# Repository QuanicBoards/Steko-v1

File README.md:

# Steko-v1
The original Steko Stenography keyboard. This repo contains KiCad PCB files for the design.

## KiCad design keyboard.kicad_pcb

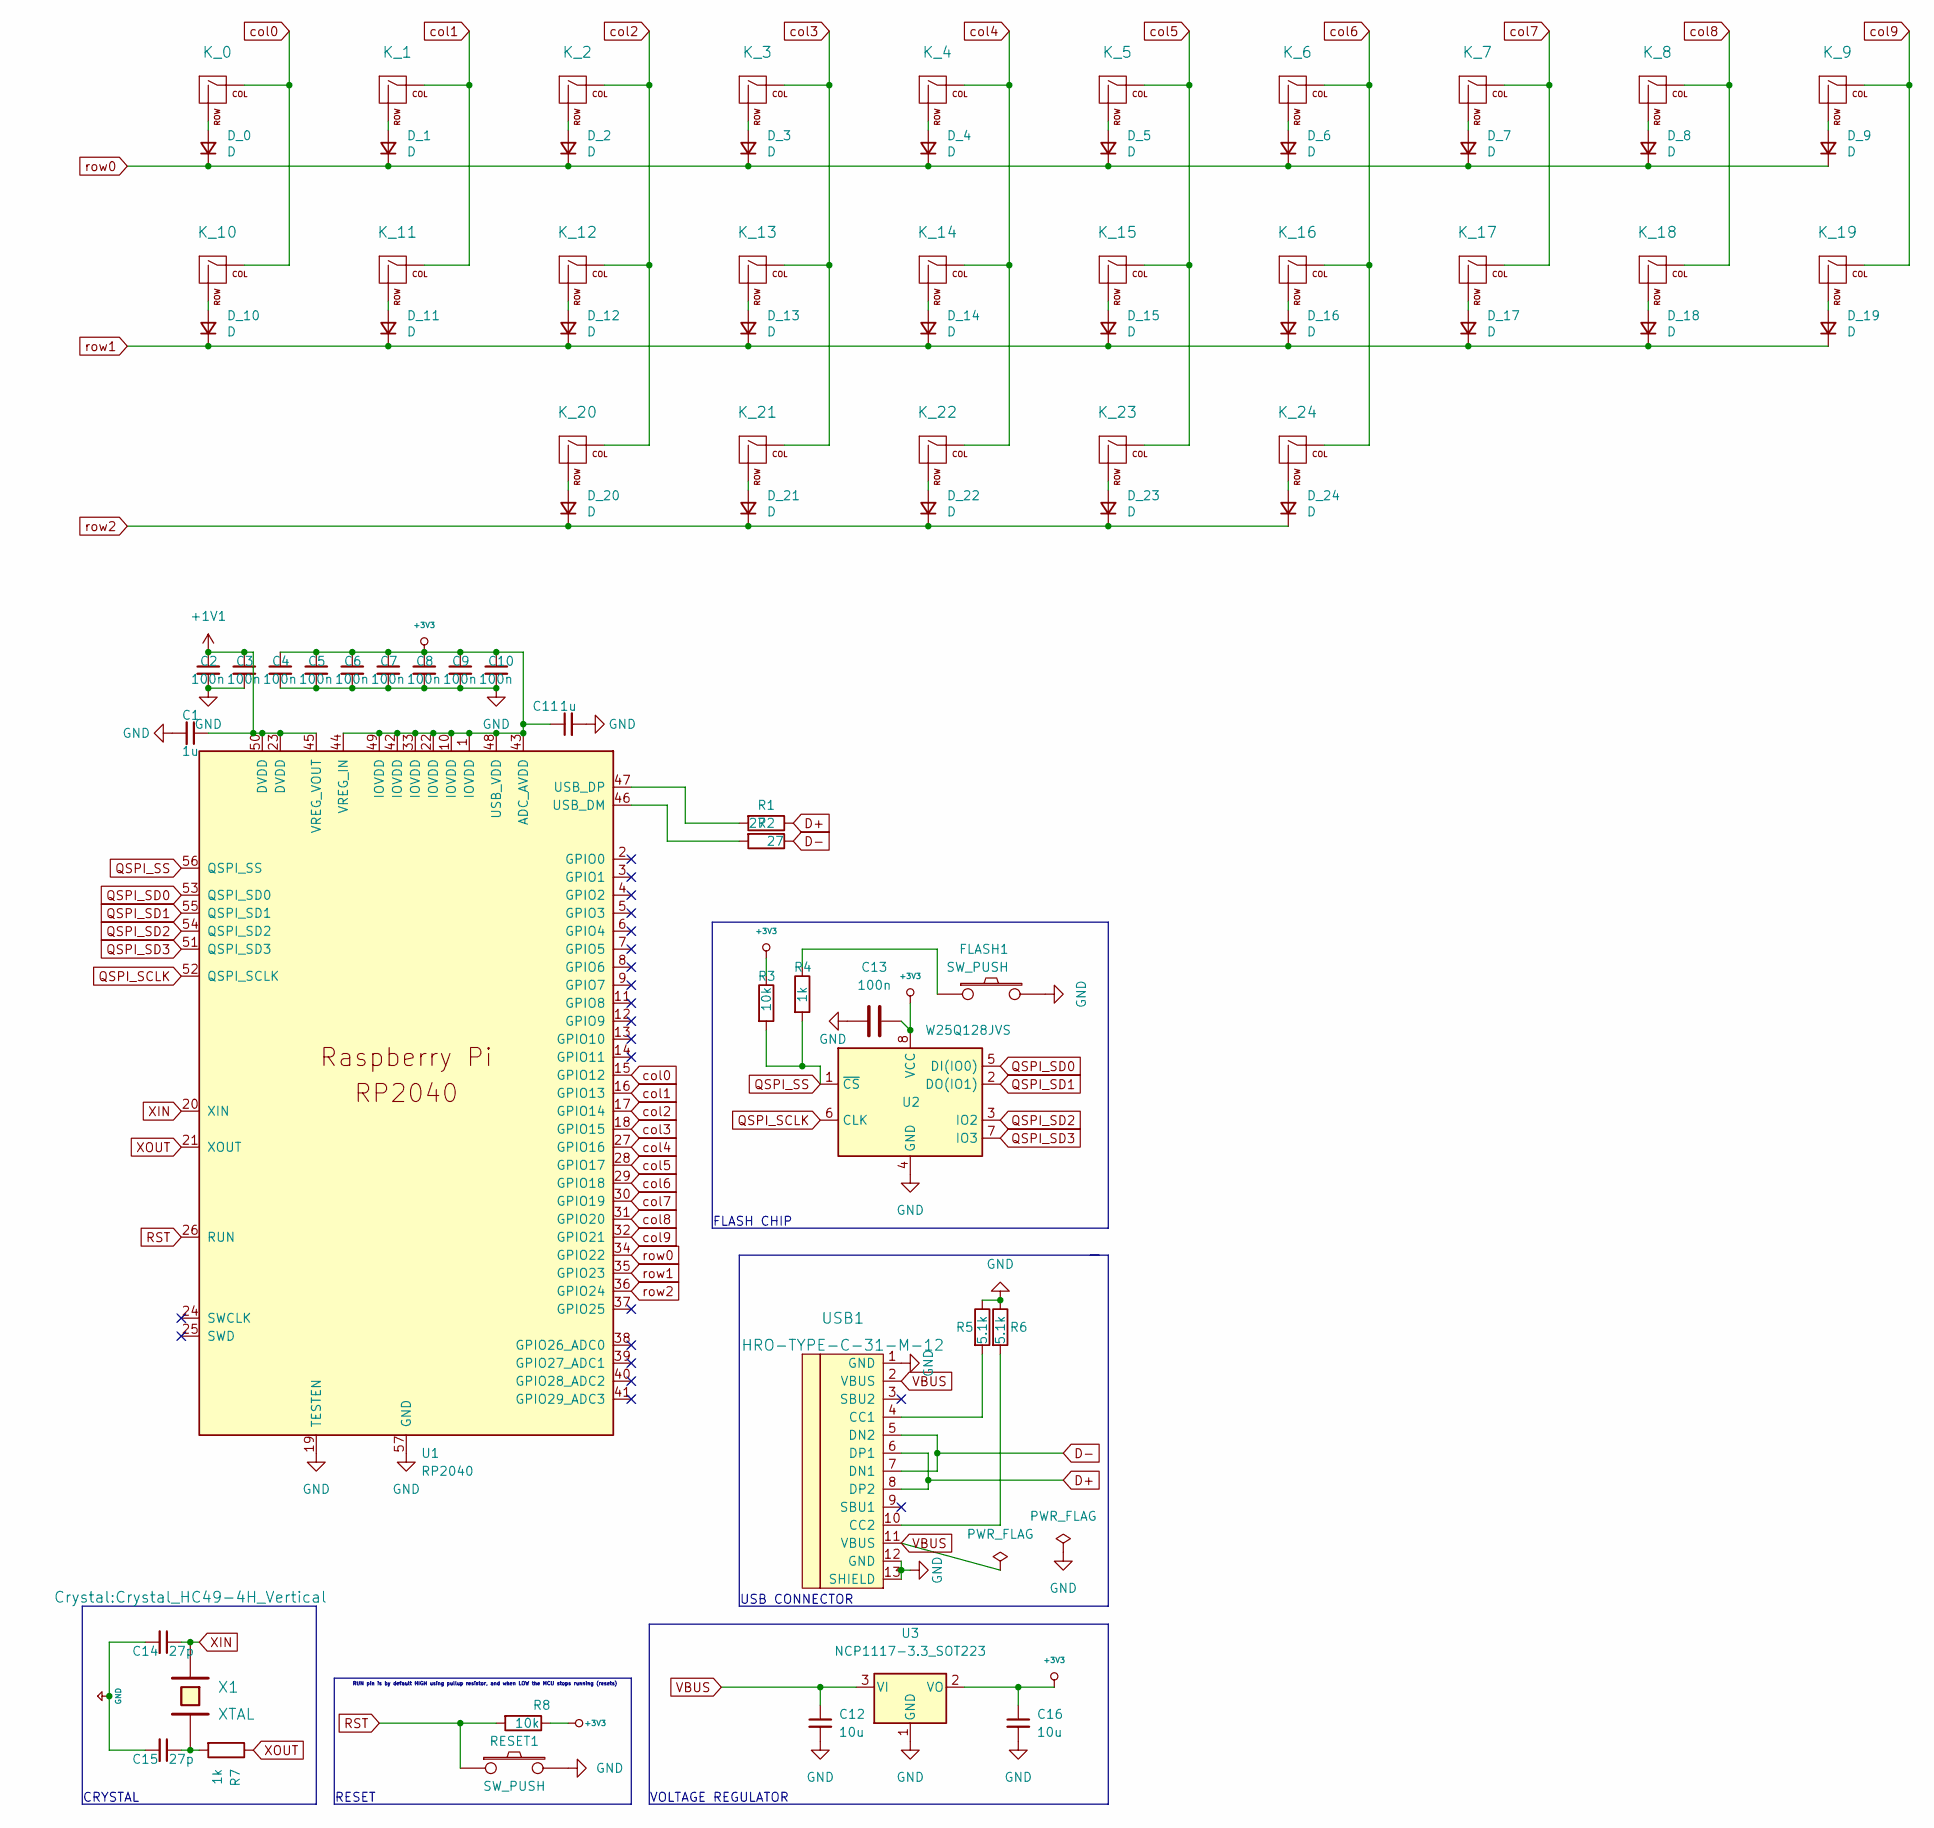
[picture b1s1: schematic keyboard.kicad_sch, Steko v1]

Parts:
C1, C11: 1u; C_1206_3216Metric
C2, C3, C4, C5, C6, C7, C8, C9, C10: 100n; C_1206_3216Metric
C12, C16: 10u; C_1206_3216Metric
C13: 100n; C_1206_3216Metric; LCSC C60474
C14, C15: 27p; C_1206_3216Metric
D_0, D_1, D_2, D_3, D_4, D_5, D_6, D_7, D_8, D_9, D_10, D_11, D_12, D_13, D_14, D_15, D_16, D_17, D_18, D_19, D_20, D_21, D_22, D_23, D_24: D; D_SOD-123
FLASH1: SW_PUSH; SW_SPST_PTS645
K_0, K_1, K_2, K_3, K_4, K_5, K_6, K_7, K_8, K_9, K_10, K_11, K_12, K_13, K_14, K_15, K_16, K_17, K_18, K_19, K_20, K_21, K_22, K_23, K_24: KEYSW; MX-1U-NoLED
R1, R2: 27; R_1206_3216Metric
R3, R8: 10k; R_1206_3216Metric
R4, R7: 1k; R_1206_3216Metric
R5, R6: 5.1k; R_1206_3216Metric
RESET1: SW_PUSH; SW_SPST_PTS645
U1: RP2040; RP2040-QFN-56
U2: W25Q128JVS; SOIC-8_5.23x5.23mm_P1.27mm; LCSC C113767
U3: NCP1117-3.3_SOT223; SOT-223-3_TabPin2
USB1: HRO-TYPE-C-31-M-12
X1: XTAL; Crystal_HC49-4H_Vertical

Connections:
+1V1: C1.1, C2.1, C3.1, U1.23 (DVDD), U1.45 (VREG_VOUT), U1.50 (DVDD)
D+: R1.1, USB1.6 (DP1), USB1.8 (DP2)
D-: R2.1, USB1.5 (DN2), USB1.7 (DN1)
unnamed: C15.1, R7.2, X1.2
unnamed: D_0.2 (A), K_0.2 (ROW)
unnamed: D_1.2 (A), K_1.2 (ROW)
unnamed: D_2.2 (A), K_2.2 (ROW)
unnamed: D_3.2 (A), K_3.2 (ROW)
unnamed: D_4.2 (A), K_4.2 (ROW)
unnamed: D_5.2 (A), K_5.2 (ROW)
unnamed: D_6.2 (A), K_6.2 (ROW)
unnamed: D_7.2 (A), K_7.2 (ROW)
unnamed: D_8.2 (A), K_8.2 (ROW)
unnamed: D_9.2 (A), K_9.2 (ROW)
unnamed: D_10.2 (A), K_10.2 (ROW)
unnamed: D_11.2 (A), K_11.2 (ROW)
unnamed: D_12.2 (A), K_12.2 (ROW)
unnamed: D_13.2 (A), K_13.2 (ROW)
unnamed: D_14.2 (A), K_14.2 (ROW)
unnamed: D_15.2 (A), K_15.2 (ROW)
unnamed: D_16.2 (A), K_16.2 (ROW)
unnamed: D_17.2 (A), K_17.2 (ROW)
unnamed: D_18.2 (A), K_18.2 (ROW)
unnamed: D_19.2 (A), K_19.2 (ROW)
unnamed: D_20.2 (A), K_20.2 (ROW)
unnamed: D_21.2 (A), K_21.2 (ROW)
unnamed: D_22.2 (A), K_22.2 (ROW)
unnamed: D_23.2 (A), K_23.2 (ROW)
unnamed: D_24.2 (A), K_24.2 (ROW)
unnamed: FLASH1.1, R4.1
unnamed: R2.2, U1.46 (USB_DM)
unnamed: R1.2, U1.47 (USB_DP)
unnamed: R5.2, USB1.4 (CC1)
unnamed: R6.2, USB1.10 (CC2)
QSPI_SCLK: U1.52 (QSPI_SCLK), U2.6 (CLK)
QSPI_SD0: U1.53 (QSPI_SD0), U2.5 (DI(IO0))
QSPI_SD1: U1.55 (QSPI_SD1), U2.2 (DO(IO1))
QSPI_SD2: U1.54 (QSPI_SD2), U2.3 (IO2)
QSPI_SD3: U1.51 (QSPI_SD3), U2.7 (IO3)
QSPI_SS: R3.2, R4.2, U1.56 (QSPI_SS), U2.1 (~CS)
RST: R8.2, RESET1.1, U1.26 (RUN)
VBUS: C12.1, U3.3 (VI), USB1.2 (VBUS), USB1.11 (VBUS)
XIN: C14.1, U1.20 (XIN), X1.1
XOUT: R7.1, U1.21 (XOUT)
col0: K_0.1 (COL), K_10.1 (COL), U1.15 (GPIO12)
col1: K_1.1 (COL), K_11.1 (COL), U1.16 (GPIO13)
col2: K_2.1 (COL), K_12.1 (COL), K_20.1 (COL), U1.17 (GPIO14)
col3: K_3.1 (COL), K_13.1 (COL), K_21.1 (COL), U1.18 (GPIO15)
col4: K_4.1 (COL), K_14.1 (COL), K_22.1 (COL), U1.27 (GPIO16)
col5: K_5.1 (COL), K_15.1 (COL), K_23.1 (COL), U1.28 (GPIO17)
col6: K_6.1 (COL), K_16.1 (COL), K_24.1 (COL), U1.29 (GPIO18)
col7: K_7.1 (COL), K_17.1 (COL), U1.30 (GPIO19)
col8: K_8.1 (COL), K_18.1 (COL), U1.31 (GPIO20)
col9: K_9.1 (COL), K_19.1 (COL), U1.32 (GPIO21)
row0: D_0.1 (K), D_1.1 (K), D_2.1 (K), D_3.1 (K), D_4.1 (K), D_5.1 (K), D_6.1 (K), D_7.1 (K), D_8.1 (K), D_9.1 (K), U1.34 (GPIO22)
row1: D_10.1 (K), D_11.1 (K), D_12.1 (K), D_13.1 (K), D_14.1 (K), D_15.1 (K), D_16.1 (K), D_17.1 (K), D_18.1 (K), D_19.1 (K), U1.35 (GPIO23)
row2: D_20.1 (K), D_21.1 (K), D_22.1 (K), D_23.1 (K), D_24.1 (K), U1.36 (GPIO24)

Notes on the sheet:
FLASH CHIP
RESET
USB CONNECTOR
CRYSTAL
RUN pin is by default HIGH using pullup resistor, and when LOW the MCU stops running (resets)
VOLTAGE REGULATOR

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
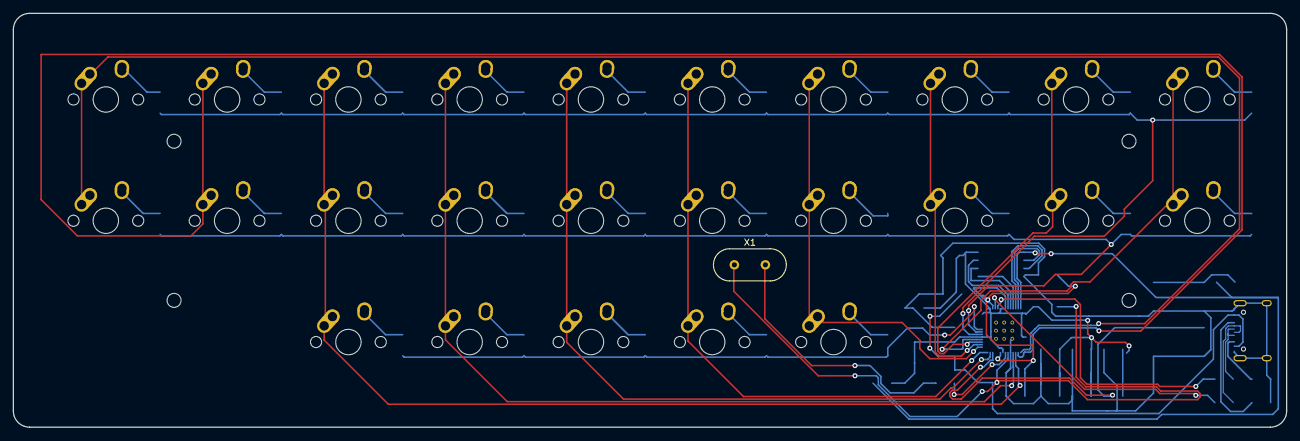
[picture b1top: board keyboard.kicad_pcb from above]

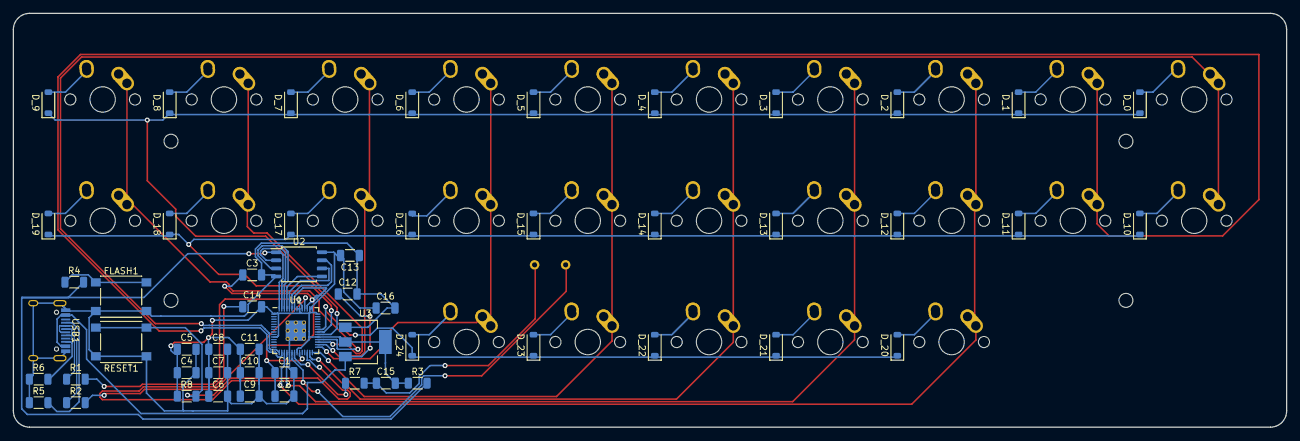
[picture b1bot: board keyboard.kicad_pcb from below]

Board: 2 copper layers, 200.0 x 65.0 mm, 85 parts (55 on the bottom side), 59 nets.

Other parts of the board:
HOLE1, HOLE2, HOLE3, HOLE4: MountingHole_2.2mm_M2_DIN965

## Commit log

2023-05-13 Create LICENSE
